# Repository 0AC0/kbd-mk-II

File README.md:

# kbd-mk-II
 A crkbd inspired keyborad.

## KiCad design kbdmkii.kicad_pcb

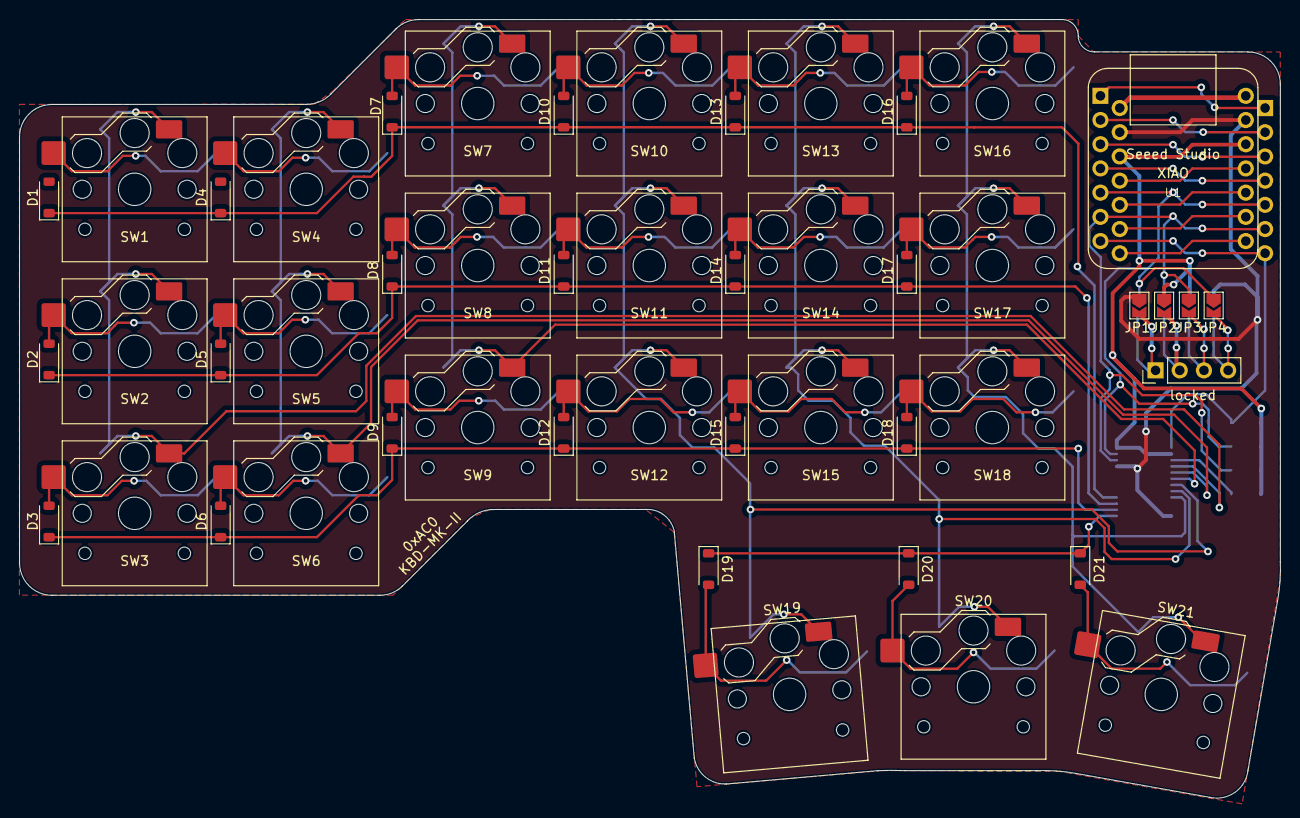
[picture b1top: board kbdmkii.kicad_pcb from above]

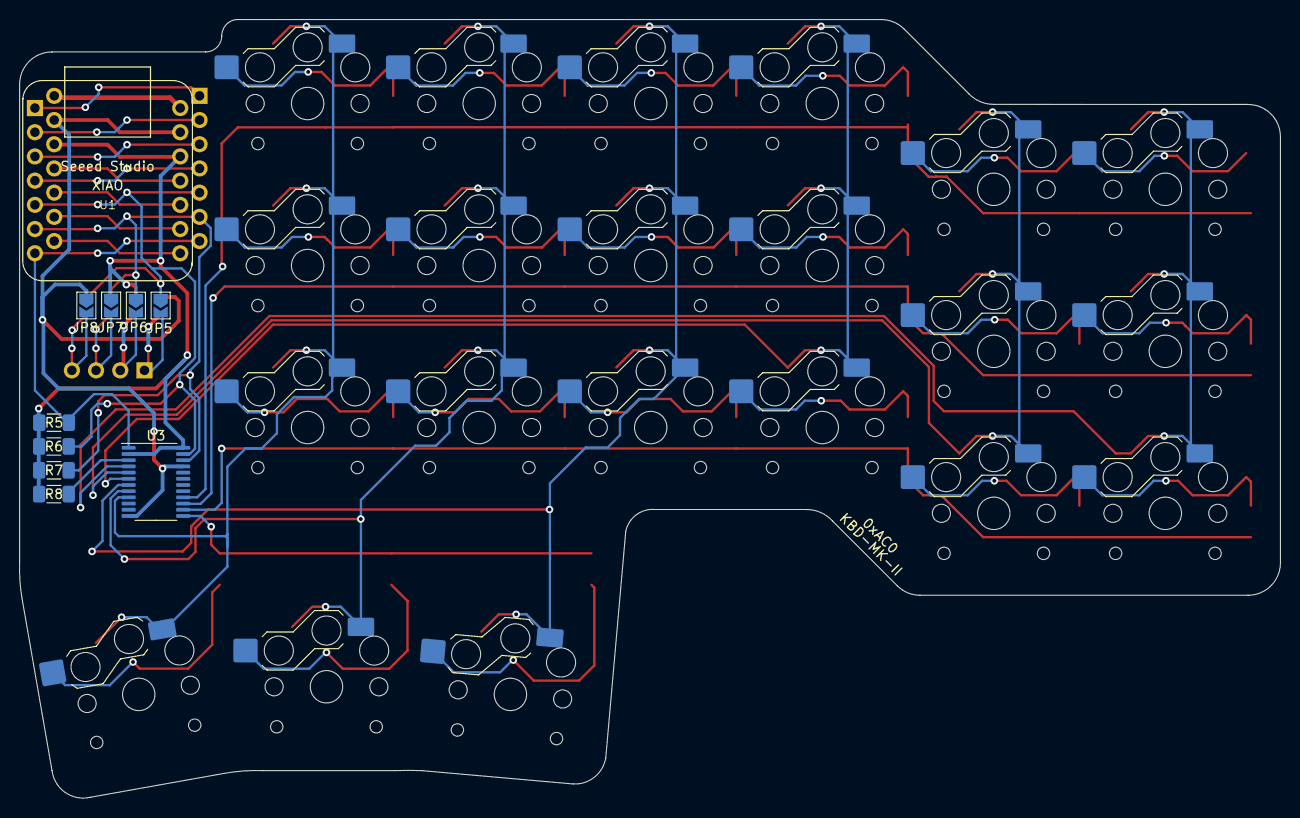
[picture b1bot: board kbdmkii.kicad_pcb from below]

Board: 2 copper layers, 132.3 x 81.7 mm, 58 parts (10 on the bottom side), 41 nets.

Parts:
D1, D2, D3, D4, D5, D6, D7, D8, D9, D10, D11, D12, D13, D14, D15, D16, D17, D18, D19, D20, D21: 1N4148W; D_SOD-123
JP1, JP2, JP3, JP4, JP5, JP6, JP7, JP8: SolderJumper-2_P1.3mm_Open_TrianglePad1.0x1.5mm
R5, R6, R7, R8: 10k; R_1206_3216Metric_Pad1.30x1.75mm_HandSolder
SW1, SW2, SW3, SW4, SW5, SW6, SW7, SW8, SW9, SW10, SW11, SW12, SW13, SW14, SW15, SW16, SW17, SW18, SW19, SW20: SW_Push; SW_Hotswap_Kailh_Choc_V1_1.00u_reversible
SW21: SW_Push; SW_Hotswap_Kailh_Choc_V1_1.50u_90deg_reversible
U1, U1#2: Seeed Studio XIAO SAMD21; XIAO-Generic-Thruhole-14P-2.54-21X17.8MM
U3: PCAL6416APW; TSSOP-24_4.4x7.8mm_P0.65mm
locked: Display_I2C; PinHeader_1x04_P2.54mm_Vertical

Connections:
+3V3: JP2.1, JP7.1, R5.1, R6.1, R7.1, R8.2, U1.12 (3V3), U1#2.12 (3V3), U3.2 (VDD_I2C), U3.24 (VDD_P)
/COL 0: SW1.1, SW2.1, SW3.1, U3.4 (P0_0)
/COL 1: SW4.1, SW5.1, SW6.1, U3.5 (P0_1)
/COL 2: SW7.1, SW8.1, SW9.1, U3.6 (P0_2)
/COL 3: SW10.1, SW11.1, SW12.1, SW19.1, U3.7 (P0_3)
/COL 4: SW13.1, SW14.1, SW15.1, SW20.1, U3.8 (P0_4)
/COL 5: SW16.1, SW17.1, SW18.1, SW21.1, U3.9 (P0_5)
/I2C_SCL: JP3.1, JP6.1, R7.2, U1.6 (PA9_A5_D5_SCL), U1#2.6 (PA9_A5_D5_SCL), U3.22 (SCL)
/I2C_SDA: JP4.1, JP5.1, R6.2, U1.5 (PA8_A4_D4_SDA), U1#2.5 (PA8_A4_D4_SDA), U3.23 (SDA)
/INT: R5.2, U1.7 (PB08_A6_D6_TX), U1#2.7 (PB08_A6_D6_TX), U3.1 (~INT)
/LINE 0: D1.1 (K), D4.1 (K), D7.1 (K), D10.1 (K), D13.1 (K), D16.1 (K), U3.16 (P1_3)
/LINE 1: D2.1 (K), D5.1 (K), D8.1 (K), D11.1 (K), D14.1 (K), D17.1 (K), U3.15 (P1_2)
/LINE 2: D3.1 (K), D6.1 (K), D9.1 (K), D12.1 (K), D15.1 (K), D18.1 (K), U3.14 (P1_1)
/LINE 3: D19.1 (K), D20.1 (K), D21.1 (K), U3.13 (P1_0)
GND: JP1.1, JP8.1, U1.13 (GND), U1#2.13 (GND), U3.12 (VSS), U3.21 (ADDR)
unnamed: D1.2 (A), SW1.2
unnamed: D2.2 (A), SW2.2
unnamed: D3.2 (A), SW3.2
unnamed: D4.2 (A), SW4.2
unnamed: D5.2 (A), SW5.2
unnamed: D6.2 (A), SW6.2
unnamed: D7.2 (A), SW7.2
unnamed: D8.2 (A), SW8.2
unnamed: D9.2 (A), SW9.2
unnamed: D10.2 (A), SW10.2
unnamed: D11.2 (A), SW11.2
unnamed: D12.2 (A), SW12.2
unnamed: D13.2 (A), SW13.2
unnamed: D14.2 (A), SW14.2
unnamed: D15.2 (A), SW15.2
unnamed: D16.2 (A), SW16.2
unnamed: D17.2 (A), SW17.2
unnamed: D18.2 (A), SW18.2
unnamed: D19.2 (A), SW19.2
unnamed: D20.2 (A), SW20.2
unnamed: D21.2 (A), SW21.2
unnamed: JP1.2, JP5.2, locked.1
unnamed: JP2.2, JP6.2, locked.2
unnamed: JP3.2, JP7.2, locked.3
unnamed: JP4.2, JP8.2, locked.4
unnamed: R8.1, U3.3 (~RESET)

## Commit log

2023-03-18 rev 2.0
2023-03-18 add ground plane
2023-03-22 improved ground plane, fixed some warnings
